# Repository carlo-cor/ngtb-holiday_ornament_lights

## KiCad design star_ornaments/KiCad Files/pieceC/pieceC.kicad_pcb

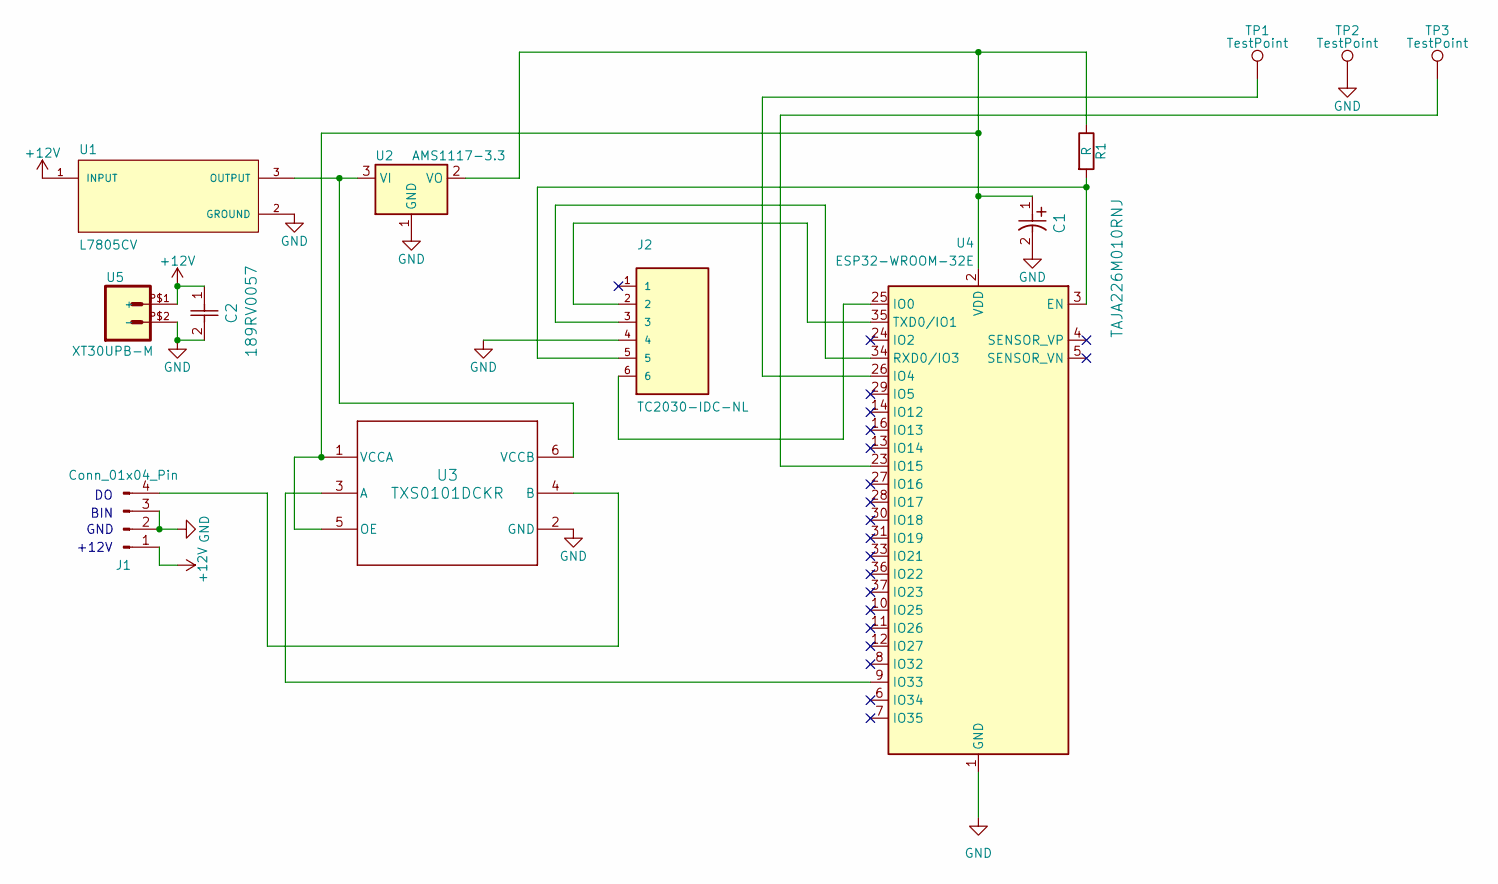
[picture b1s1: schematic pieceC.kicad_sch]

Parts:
C1: TAJA226M010RNJ; TAJA_AVX
C2: 189RV0057; CAP_SMD_6p3x7p7_KNC
J1: Conn_01x04_Pin; PinHeader_1x04_P2.54mm_Vertical
J2: TC2030-IDC-NL; TAG_TC2030-IDC-NL; PARTREV MS
R1: R; RESC3115X65N
TP1, TP2, TP3: TestPoint; TestPoint_Pad_1.0x1.0mm
U1: L7805CV; TO255P1040X460X1968-3; PARTREV 36
U2: AMS1117-3.3; SOT-223-3_TabPin2
U3: TXS0101DCKR; DCK0006A_L
U4: ESP32-WROOM-32E
U5: XT30UPB-M

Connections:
+12V: C2.1, J1.1, U1.1 (INPUT), U5.P$1 (+)
GND: C1.2, C2.2, J1.2, J1.3, J2.4, TP2.1, U1.2 (GROUND), U2.1 (GND), U3.2 (GND), U4.1 (GND), U4.15 (GND), U4.38 (GND), U4.39 (GND), U5.P$2 (-)
unnamed: J1.4, U3.4 (B)
unnamed: U1.3 (OUTPUT), U2.3 (VI), U3.6 (VCCB)
unnamed: C1.1, R1.1, U2.2 (VO), U3.1 (VCCA), U3.5 (OE), U4.2 (VDD)
unnamed: U3.3 (A), U4.9 (IO33)
unnamed: J2.5, R1.2, U4.3 (EN)
unnamed: J2.6, U4.25 (IO0)
unnamed: TP1.1, U4.26 (IO4)
unnamed: TP3.1, U4.23 (IO15)
unnamed: J2.3, U4.34 (RXD0/IO3)
unnamed: J2.2, U4.35 (TXD0/IO1)

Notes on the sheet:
BIN
GND
+12V

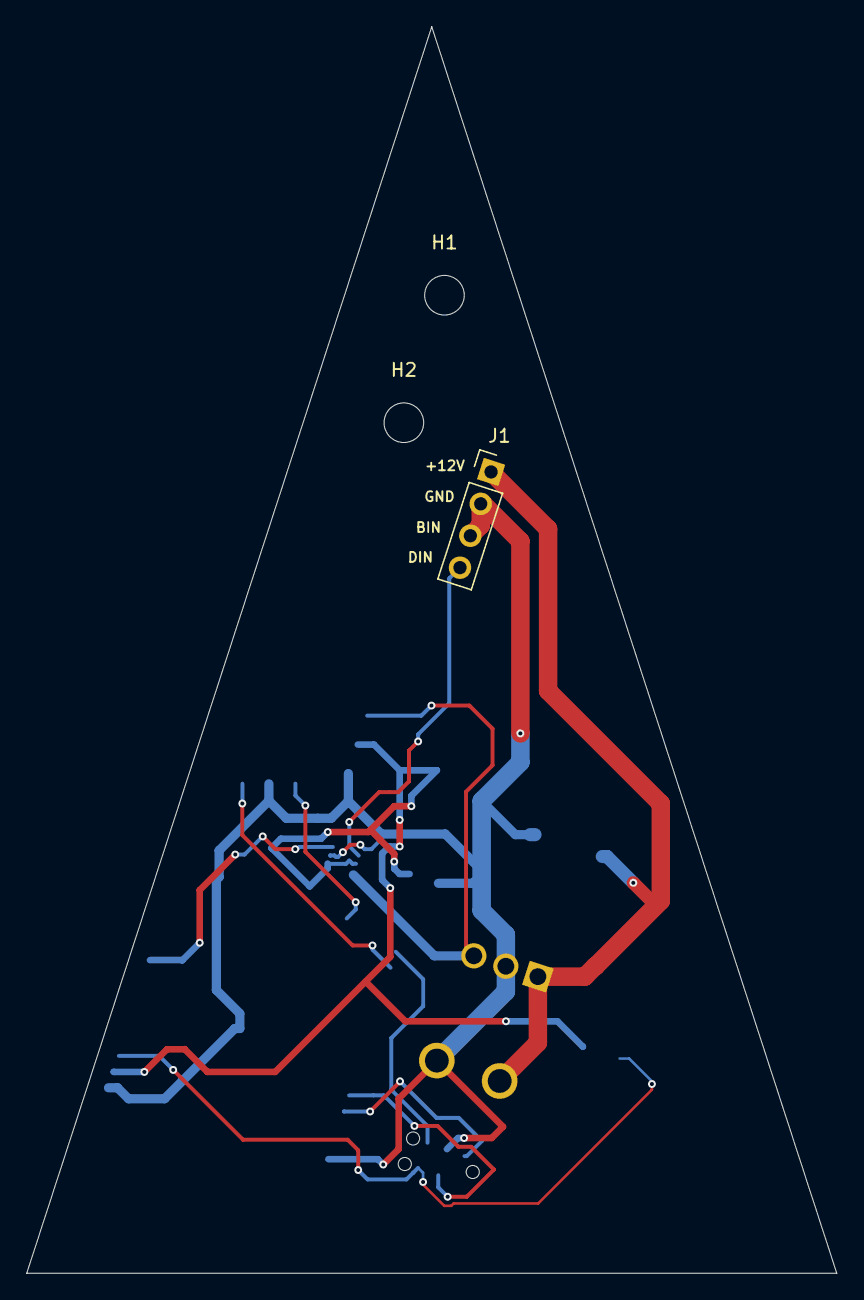
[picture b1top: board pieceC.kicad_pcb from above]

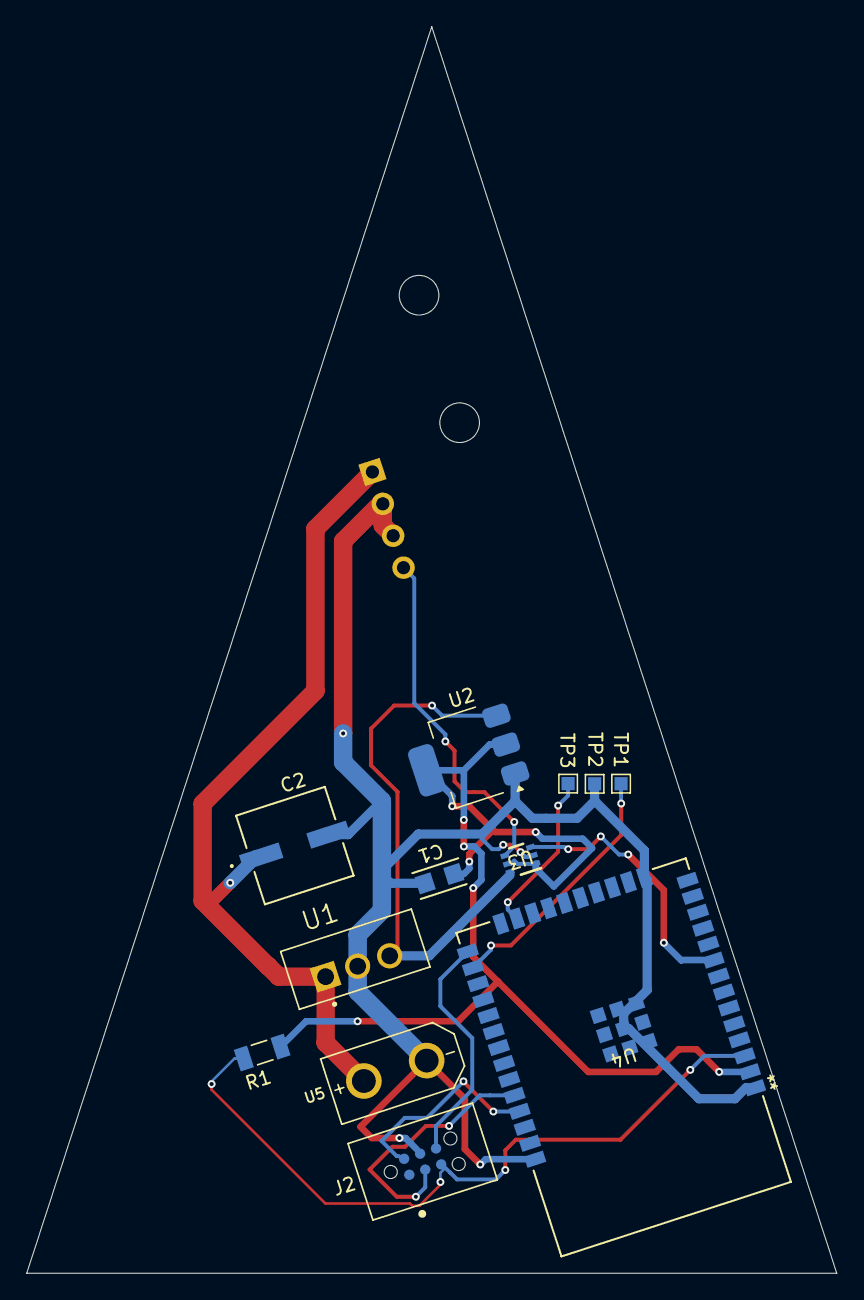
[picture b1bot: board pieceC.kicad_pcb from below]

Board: 2 copper layers, 61.3 x 94.4 mm, 15 parts (12 on the bottom side), 12 nets.

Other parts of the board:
H1, H2: MountingHole_3mm

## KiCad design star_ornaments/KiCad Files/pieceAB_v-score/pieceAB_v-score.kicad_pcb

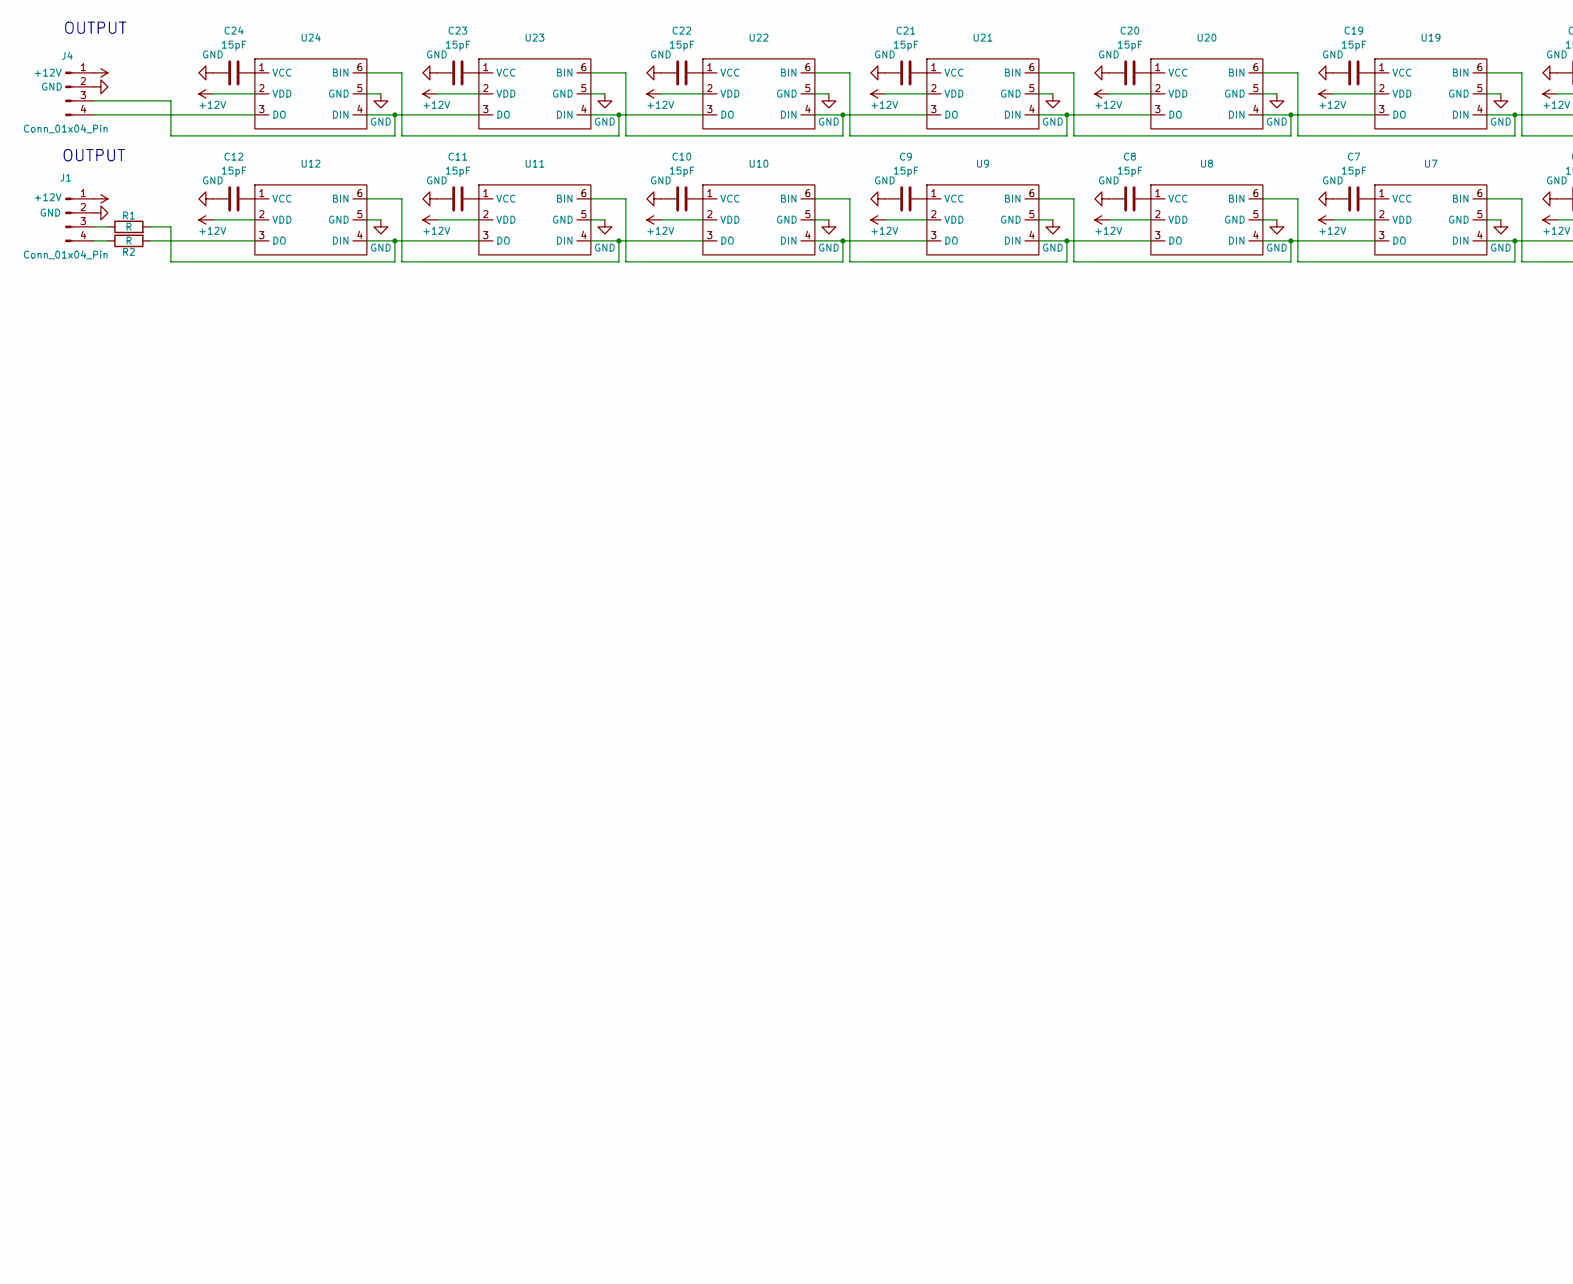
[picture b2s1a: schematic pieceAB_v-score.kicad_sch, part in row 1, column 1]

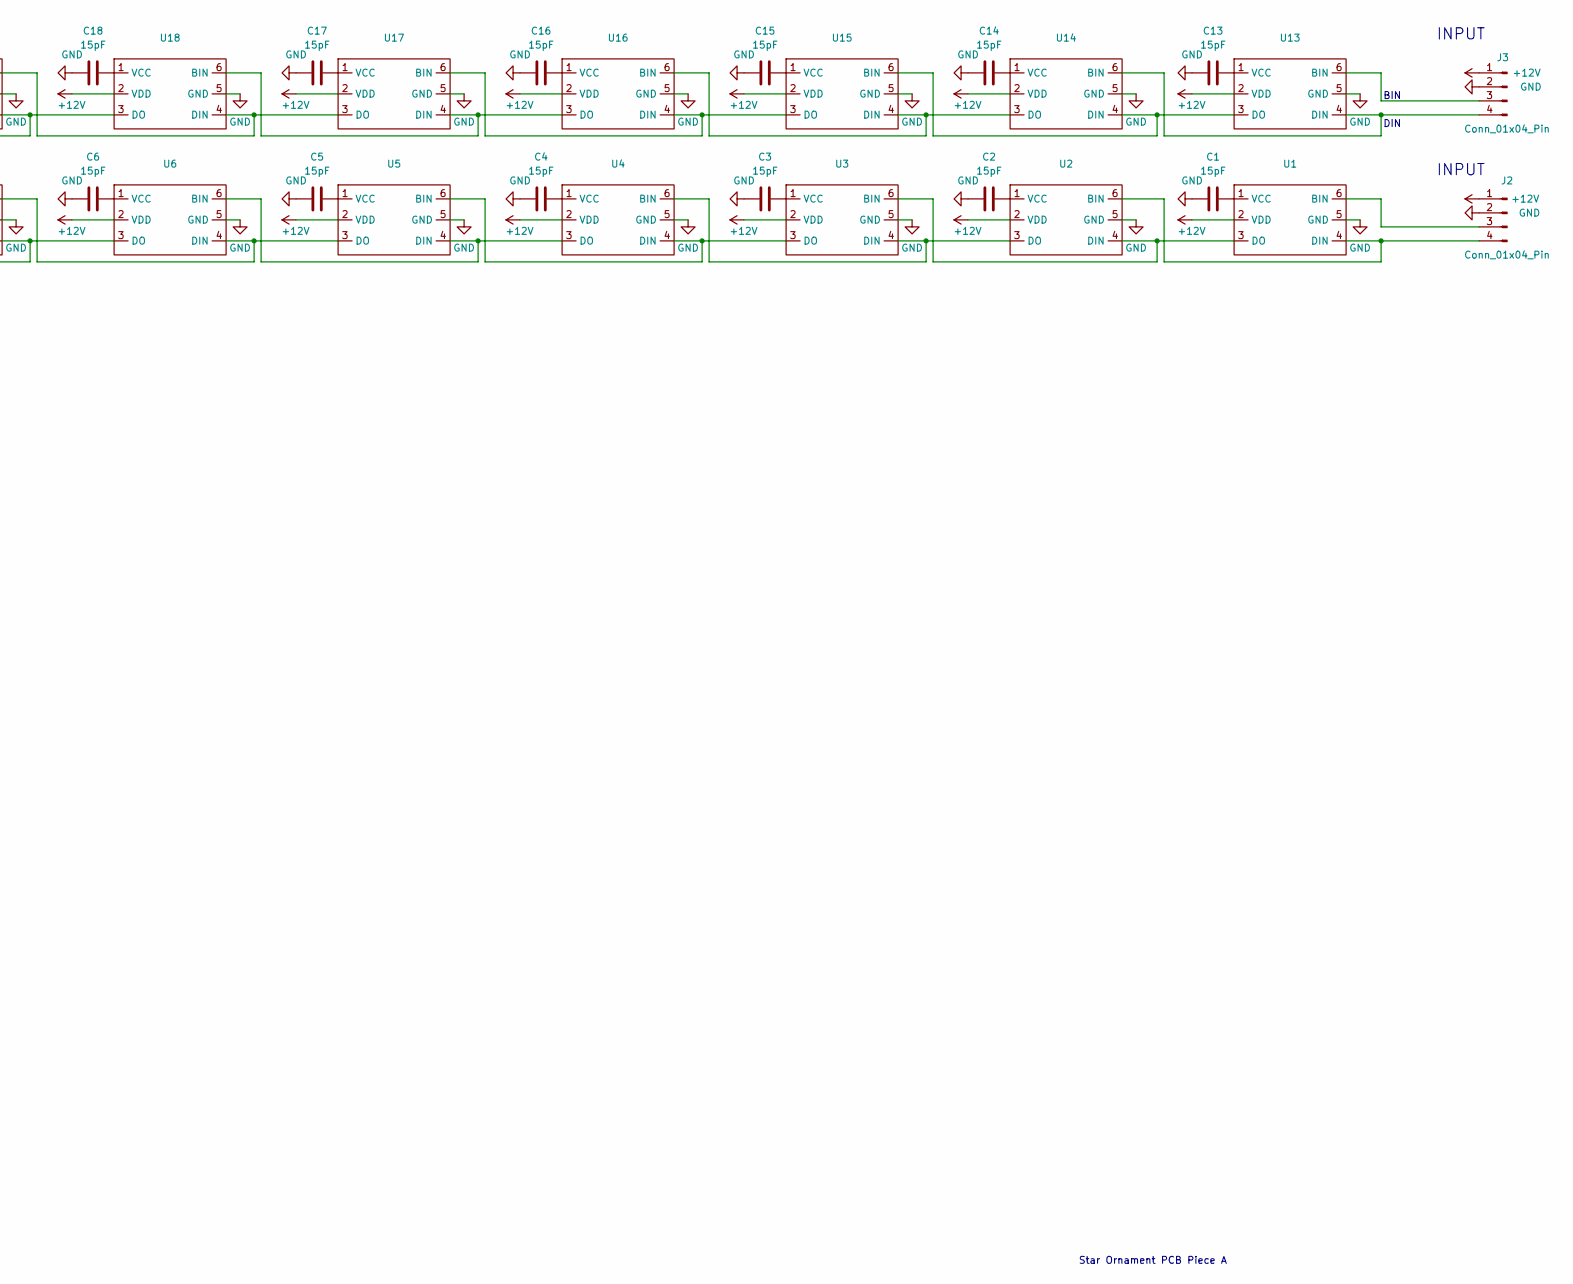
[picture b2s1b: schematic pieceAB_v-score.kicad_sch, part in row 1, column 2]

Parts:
C1, C2, C3, C4, C5, C6, C7, C8, C9, C10, C11, C12, C13, C14, C15, C16, C17, C18, C19, C20, C21, C22, C23, C24: 15pF; CAPC1005X55N
J1, J2, J3, J4: Conn_01x04_Pin; PinHeader_1x04_P2.54mm_Vertical
R1, R2: R; RESC1608X55N
U1, U2, U3, U4, U5, U6, U7, U8, U9, U10, U11, U12, U13, U14, U15, U16, U17, U18, U19, U20, U21, U22, U23, U24: LED-TRICOLOR-5050

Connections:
+12V: J1.1, J2.1, J3.1, J4.1, U1.2 (VDD), U2.2 (VDD), U3.2 (VDD), U4.2 (VDD), U5.2 (VDD), U6.2 (VDD), U7.2 (VDD), U8.2 (VDD), U9.2 (VDD), U10.2 (VDD), U11.2 (VDD), U12.2 (VDD), U13.2 (VDD), U14.2 (VDD), U15.2 (VDD), U16.2 (VDD), U17.2 (VDD), U18.2 (VDD), U19.2 (VDD), U20.2 (VDD), U21.2 (VDD), U22.2 (VDD), U23.2 (VDD), U24.2 (VDD)
GND: C1.2, C2.2, C3.2, C4.2, C5.2, C6.2, C7.2, C8.2, C9.2, C10.2, C11.2, C12.2, C13.2, C14.2, C15.2, C16.2, C17.2, C18.2, C19.2, C20.2, C21.2, C22.2, C23.2, C24.2, J1.2, J2.2, J3.2, J4.2, U1.5 (GND), U2.5 (GND), U3.5 (GND), U4.5 (GND), U5.5 (GND), U6.5 (GND), U7.5 (GND), U8.5 (GND), U9.5 (GND), U10.5 (GND), U11.5 (GND), U12.5 (GND), U13.5 (GND), U14.5 (GND), U15.5 (GND), U16.5 (GND), U17.5 (GND), U18.5 (GND), U19.5 (GND), U20.5 (GND), U21.5 (GND), U22.5 (GND), U23.5 (GND), U24.5 (GND)
unnamed: J1.3, R1.1
unnamed: J1.4, R2.1
unnamed: J2.3, U1.6 (BIN)
unnamed: J2.4, U1.4 (DIN), U2.6 (BIN)
unnamed: J3.3, U13.6 (BIN)
unnamed: J3.4, U13.4 (DIN), U14.6 (BIN)
unnamed: J4.3, U23.3 (DO), U24.4 (DIN)
unnamed: J4.4, U24.3 (DO)
unnamed: U1.3 (DO), U2.4 (DIN), U3.6 (BIN)
unnamed: C1.1, U1.1 (VCC)
unnamed: U2.3 (DO), U3.4 (DIN), U4.6 (BIN)
unnamed: C2.1, U2.1 (VCC)
unnamed: U3.3 (DO), U4.4 (DIN), U5.6 (BIN)
unnamed: C3.1, U3.1 (VCC)
unnamed: U4.3 (DO), U5.4 (DIN), U6.6 (BIN)
unnamed: C4.1, U4.1 (VCC)
unnamed: U5.3 (DO), U6.4 (DIN), U7.6 (BIN)
unnamed: C5.1, U5.1 (VCC)
unnamed: U6.3 (DO), U7.4 (DIN), U8.6 (BIN)
unnamed: C6.1, U6.1 (VCC)
unnamed: U7.3 (DO), U8.4 (DIN), U9.6 (BIN)
unnamed: C7.1, U7.1 (VCC)
unnamed: C8.1, U8.1 (VCC)
unnamed: C9.1, U9.1 (VCC)
unnamed: U8.3 (DO), U9.4 (DIN), U10.6 (BIN)
unnamed: U9.3 (DO), U10.4 (DIN), U11.6 (BIN)
unnamed: U10.3 (DO), U11.4 (DIN), U12.6 (BIN)
unnamed: C10.1, U10.1 (VCC)
unnamed: R1.2, U11.3 (DO), U12.4 (DIN)
unnamed: C11.1, U11.1 (VCC)
unnamed: R2.2, U12.3 (DO)
unnamed: C12.1, U12.1 (VCC)
unnamed: U13.3 (DO), U14.4 (DIN), U15.6 (BIN)
unnamed: C13.1, U13.1 (VCC)
unnamed: U14.3 (DO), U15.4 (DIN), U16.6 (BIN)
unnamed: C14.1, U14.1 (VCC)
unnamed: U15.3 (DO), U16.4 (DIN), U17.6 (BIN)
unnamed: C15.1, U15.1 (VCC)
unnamed: U16.3 (DO), U17.4 (DIN), U18.6 (BIN)
unnamed: C16.1, U16.1 (VCC)
unnamed: U17.3 (DO), U18.4 (DIN), U19.6 (BIN)
unnamed: C17.1, U17.1 (VCC)
unnamed: U18.3 (DO), U19.4 (DIN), U20.6 (BIN)
unnamed: C18.1, U18.1 (VCC)
unnamed: U19.3 (DO), U20.4 (DIN), U21.6 (BIN)
unnamed: C19.1, U19.1 (VCC)
unnamed: U20.3 (DO), U21.4 (DIN), U22.6 (BIN)
unnamed: C20.1, U20.1 (VCC)
unnamed: U21.3 (DO), U22.4 (DIN), U23.6 (BIN)
unnamed: C21.1, U21.1 (VCC)
unnamed: U22.3 (DO), U23.4 (DIN), U24.6 (BIN)
unnamed: C22.1, U22.1 (VCC)
unnamed: C23.1, U23.1 (VCC)
unnamed: C24.1, U24.1 (VCC)

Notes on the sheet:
DIN
OUTPUT
BIN
INPUT
Star Ornament PCB Piece A

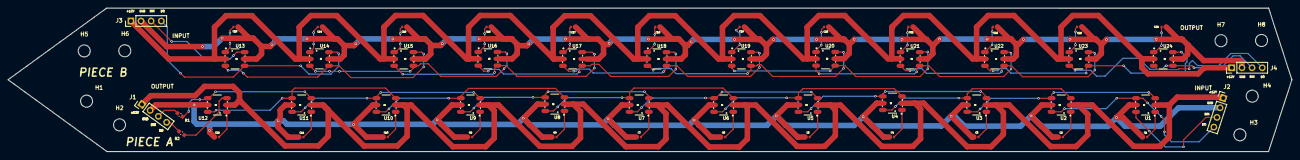
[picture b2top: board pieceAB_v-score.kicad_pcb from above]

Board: 2 copper layers, 320.9 x 35.9 mm, 62 parts (0 on the bottom side), 56 nets.

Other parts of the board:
H1, H2, H3, H4, H5, H6, H7, H8: MountingHole_3mm

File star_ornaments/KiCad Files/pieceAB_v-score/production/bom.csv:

Designator,Footprint,Quantity,Value,LCSC Part #
"C1, C10, C11, C12, C13, C14, C15, C16, C17, C18, C19, C2, C20, C21, C22, C23, C24, C3, C4, C5, C6, C7, C8, C9",CAPC1005X55N,24,15pF,
"J1, J2, J3, J4",PinHeader_1x04_P2.54mm_Vertical,4,Conn_01x04_Pin,
"R1, R2",RESC1608X55N,2,R,
"U1, U10, U11, U12, U13, U14, U15, U16, U17, U18, U19, U2, U20, U21, U22, U23, U24, U3, U4, U5, U6, U7, U8, U9",LED-TRICOLOR-5050,24,~,

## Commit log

2026-01-14 Initial commit; version 2 of the lights
2026-01-23 Fixed ESP32 footprint to correct version.
2026-01-23 Reorganized folders; made a folder containing previous releases.
